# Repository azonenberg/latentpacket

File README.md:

# latentpacket
The LATENTPACKET network infrastructure platform

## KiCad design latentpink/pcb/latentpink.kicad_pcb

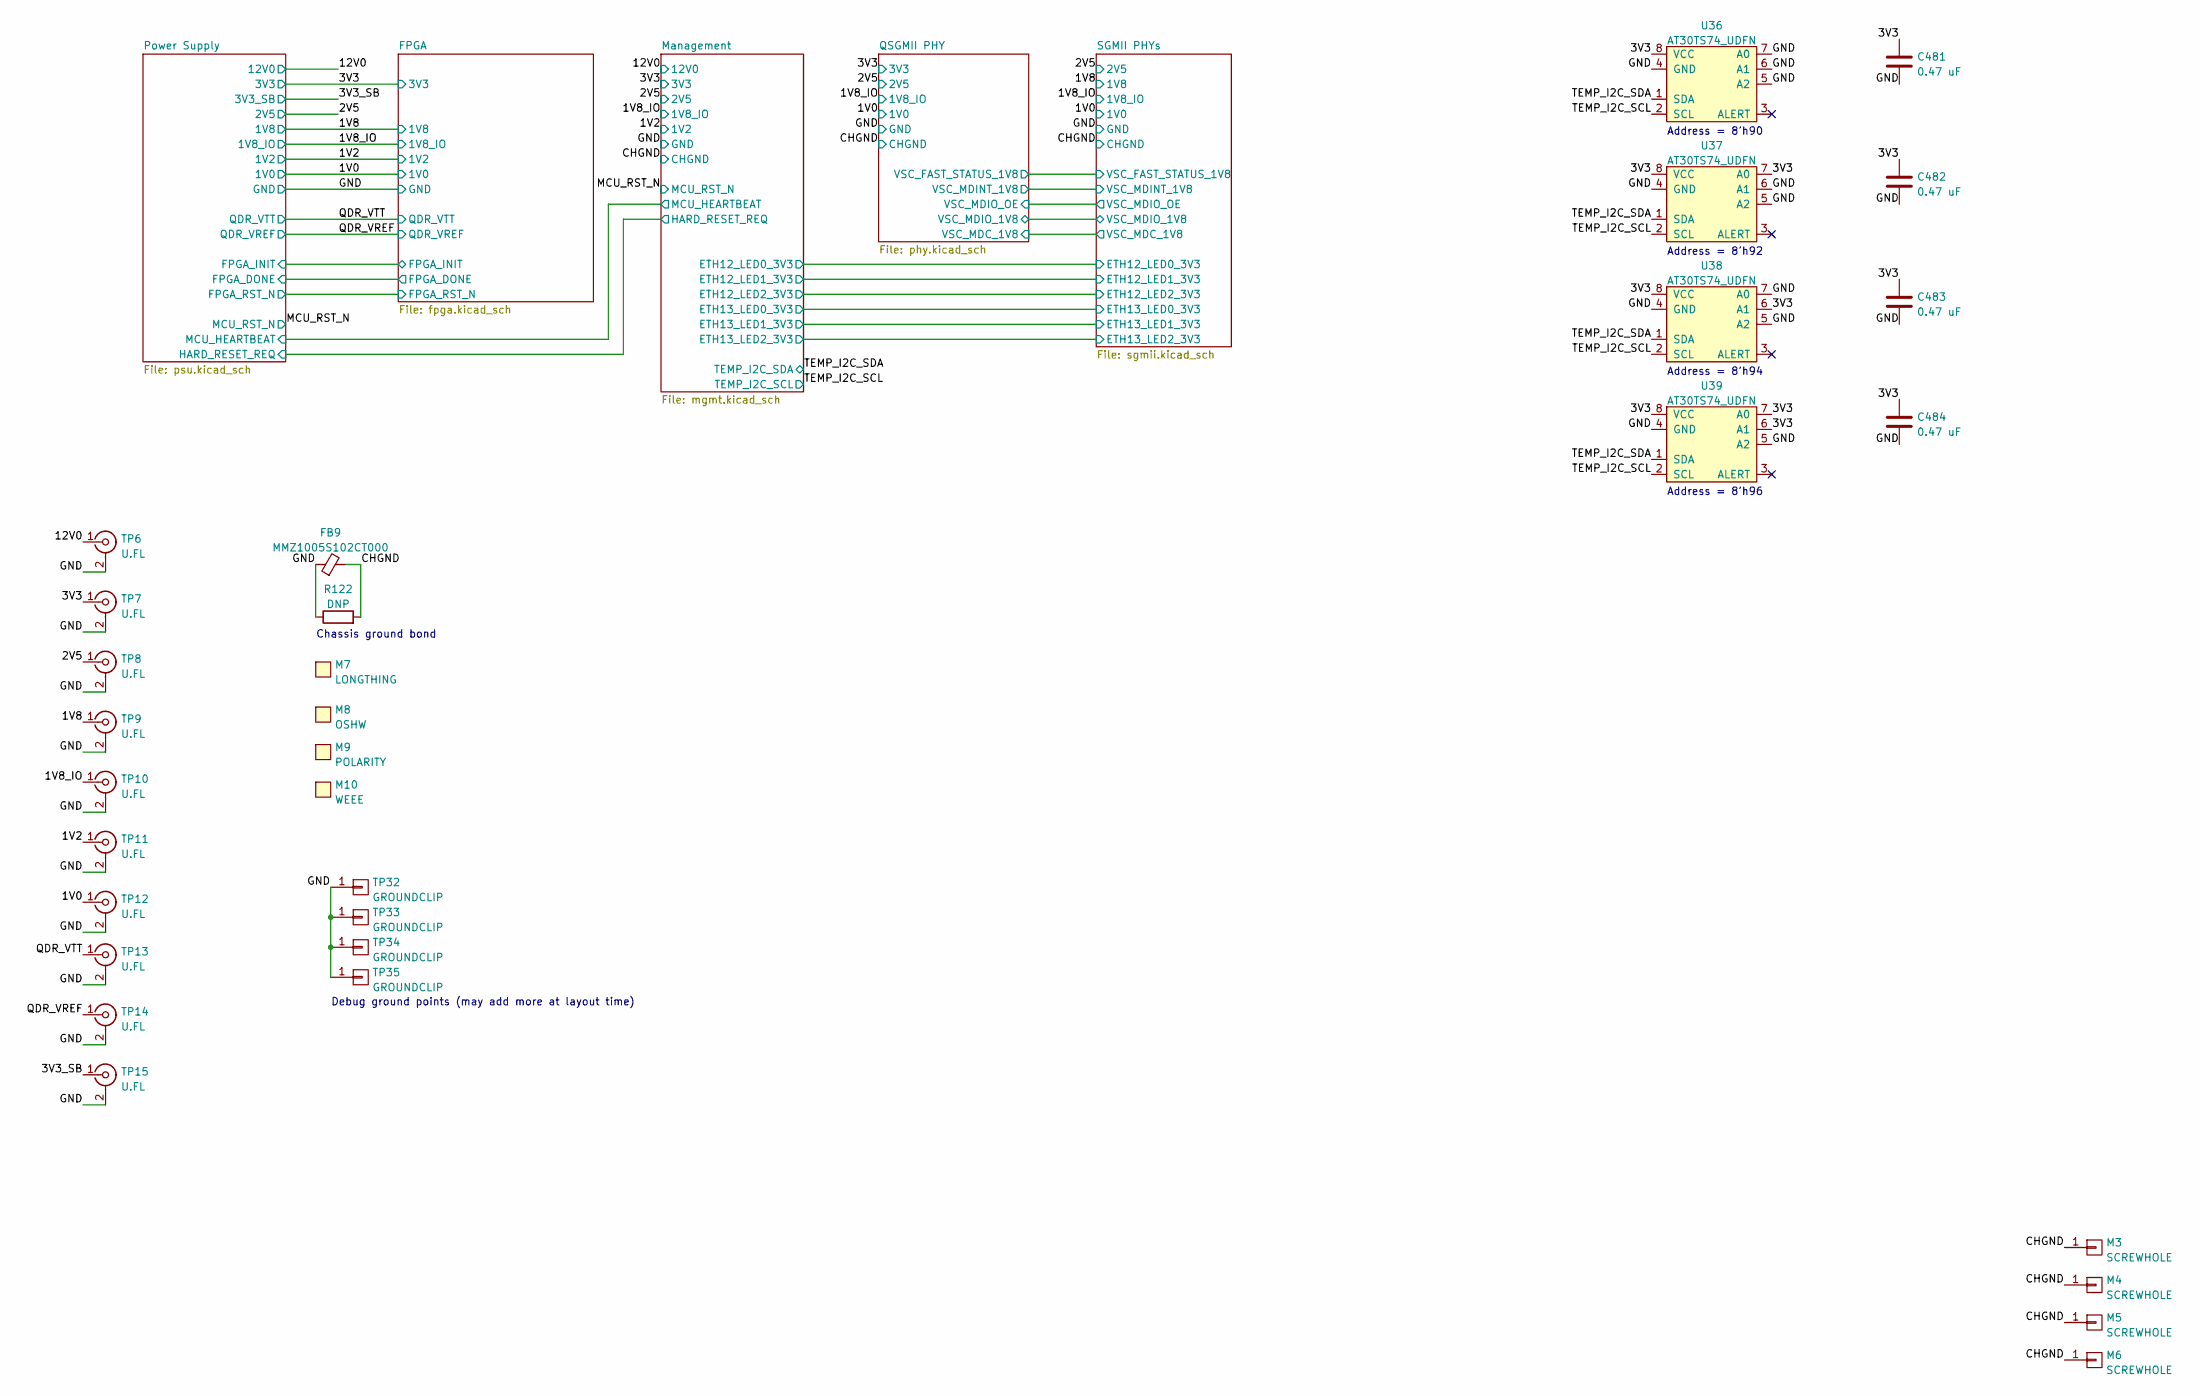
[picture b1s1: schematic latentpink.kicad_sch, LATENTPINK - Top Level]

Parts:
C481, C482, C483, C484: 0.47 uF; EIA_0402_CAP_NOSILK
FB9: MMZ1005S102CT000; EIA_0402_CAP_NOSILK
M3, M4, M5, M6: SCREWHOLE; MECHANICAL_CLEARANCEHOLE_4_40
M7: LONGTHING; LONGTHING-1200DPI
M8: OSHW; Logo_silk_OSHW_6x6mm
M9: POLARITY; Logo_silk_polarity_center_5x1.4mm
M10: WEEE; Logo_silk_WEEE_3.4x5mm
R122: DNP; EIA_1206_CAP_NOSILK
TP6, TP7, TP8, TP9, TP10, TP11, TP12, TP13, TP14, TP15: U.FL; CONN_U.FL_TE_1909763-1
TP32, TP33, TP34, TP35: GROUNDCLIP; TESTPOINT_SMT_KEYSTONE_5016
U36, U37, U38, U39: AT30TS74_UDFN; DFN_8_0.5MM_2x3MM_TALL

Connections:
/1V0: TP12.1 (In); also elsewhere on the board
/1V2: TP11.1 (In); also elsewhere on the board
/1V8: TP9.1 (In); also elsewhere on the board
/1V8_IO: TP10.1 (In); also elsewhere on the board
/2V5: TP8.1 (In); also elsewhere on the board
/3V3: C481.1, C482.1, C483.1, C484.1, TP7.1 (In), U36.8 (VCC), U37.7 (A0), U37.8 (VCC), U38.6 (A1), U38.8 (VCC), U39.6 (A1), U39.7 (A0), U39.8 (VCC); also elsewhere on the board
/3V3_SB: TP15.1 (In); also elsewhere on the board
/12V0: TP6.1 (In); also elsewhere on the board
/CHGND: FB9.2, M3.1, M4.1, M5.1, M6.1, R122.2; also elsewhere on the board
/GND: C481.2, C482.2, C483.2, C484.2, FB9.1, R122.1, TP6.2 (Ext), TP7.2 (Ext), TP8.2 (Ext), TP9.2 (Ext), TP10.2 (Ext), TP11.2 (Ext), TP12.2 (Ext), TP13.2 (Ext), TP14.2 (Ext), TP15.2 (Ext), TP32.1, TP33.1, TP34.1, TP35.1, U36.4 (GND), U36.5 (A2), U36.6 (A1), U36.7 (A0), U37.4 (GND), U37.5 (A2), U37.6 (A1), U38.4 (GND), U38.5 (A2), U38.7 (A0), U39.4 (GND), U39.5 (A2); also elsewhere on the board
/QDR_VREF: TP14.1 (In); also elsewhere on the board
/QDR_VTT: TP13.1 (In); also elsewhere on the board
/TEMP_I2C_SCL: U36.2 (SCL), U37.2 (SCL), U38.2 (SCL), U39.2 (SCL); also elsewhere on the board
/TEMP_I2C_SDA: U36.1 (SDA), U37.1 (SDA), U38.1 (SDA), U39.1 (SDA); also elsewhere on the board

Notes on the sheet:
Address = 8'h90
Chassis ground bond
Address = 8'h94
Address = 8'h92
Address = 8'h96
Debug ground points (may add more at layout time)

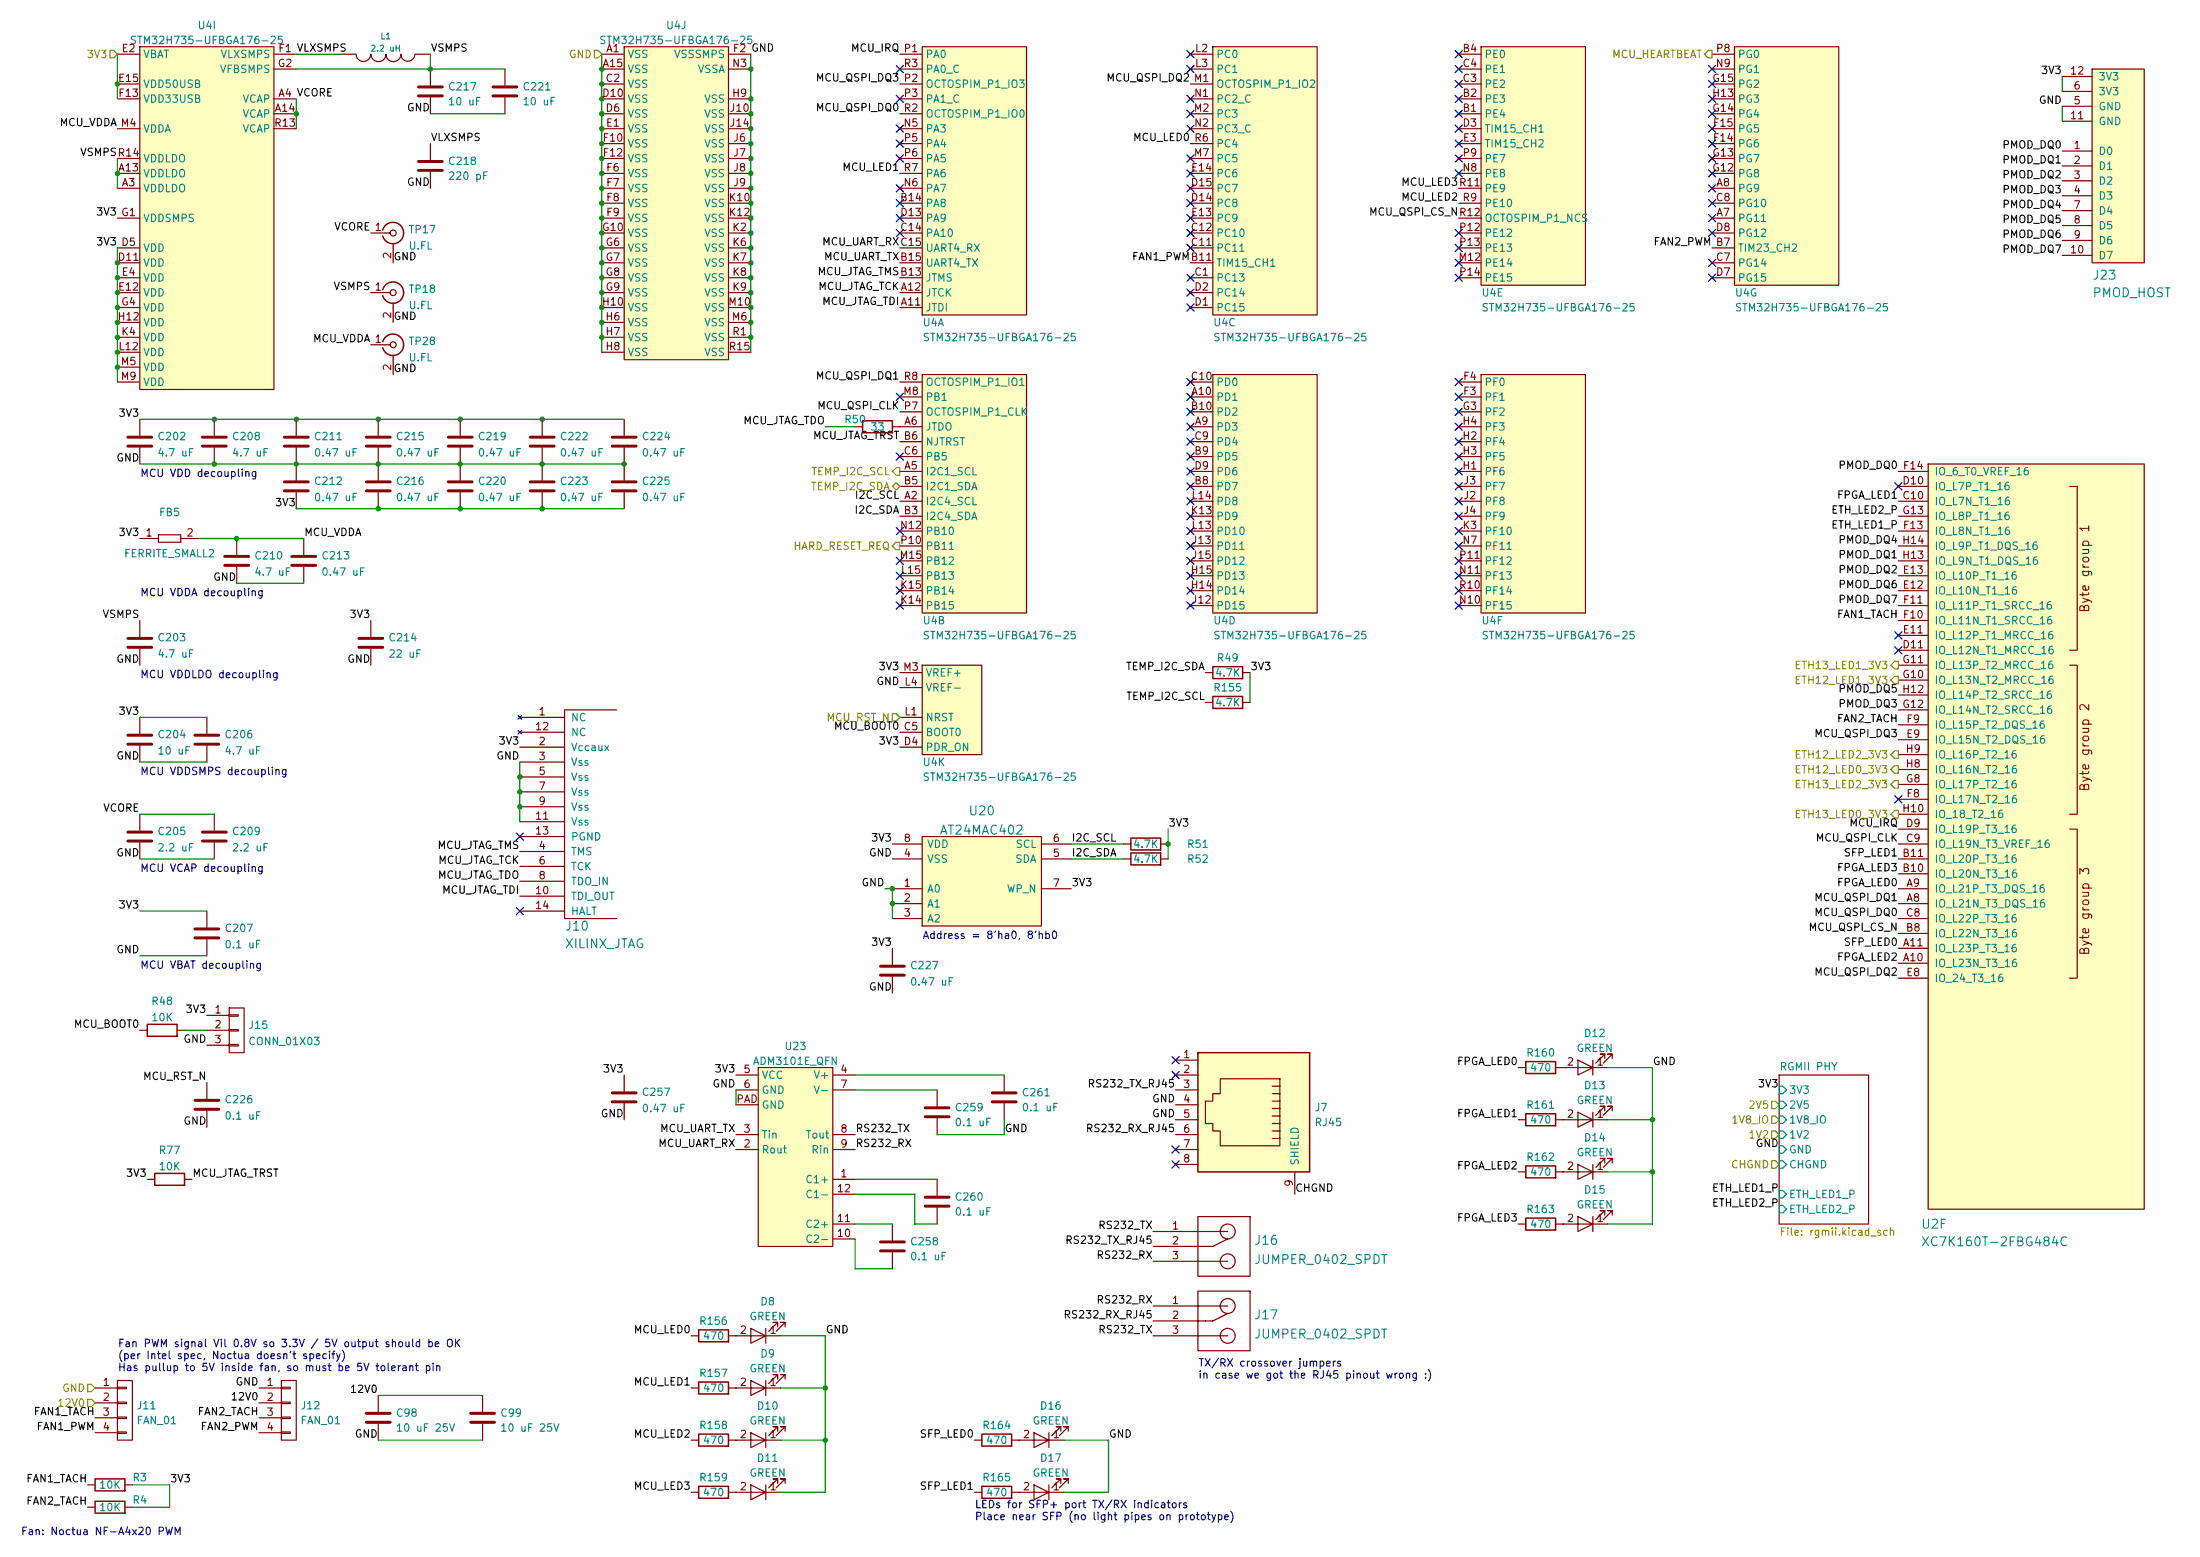
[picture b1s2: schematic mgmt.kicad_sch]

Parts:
C98, C99: 10 uF 25V; EIA_1210_CAP_NOSILK
C202, C203, C206, C208, C210: 4.7 uF; EIA_0603_CAP_NOSILK
C204, C217, C221: 10 uF; EIA_0805_CAP_NOSILK
C205, C209: 2.2 uF; EIA_0603_CAP_NOSILK
C207, C226, C258, C259, C260, C261: 0.1 uF; EIA_0402_CAP_NOSILK
C211, C212, C213, C215, C216, C219, C220, C222, C223, C224, C225, C227, C257: 0.47 uF; EIA_0402_CAP_NOSILK
C214: 22 uF; EIA_1206_CAP_NOSILK
C218: 220 pF; EIA_0402_CAP_NOSILK
D8, D9, D10, D11, D12, D13, D14, D15, D16, D17: GREEN; EIA_0603_LED
FB5: FERRITE_SMALL2; EIA_0603_INDUCTOR_NOSILK
J7: RJ45; CONN_RJ45_BELSTEWART_SS-7188S-A-PG4-1-BA-xx
J10: XILINX_JTAG; XILINX_JTAG_PTH_MOLEX_0878311420
J11, J12: FAN_01; CONN_MOLEX_KK_0470531000
J15: CONN_01X03; CONN_HEADER_2.54MM_1x3
J16, J17: JUMPER_0402_SPDT; EIA_0402_JUMPER
J23: PMOD_HOST; CONN_HEADER_2.54MM_2x6_RA_PMOD_HOST
L1: 2.2 uH; EIA_1210_CAP_NOSILK
R3, R4, R48, R77: 10K; EIA_0402_RES_NOSILK
R49, R51, R52, R155: 4.7K; EIA_0402_RES_NOSILK
R50: 33; EIA_0402_RES_NOSILK
R156, R157, R158, R159, R160, R161, R162, R163, R164, R165: 470; EIA_0402_RES_NOSILK
TP17, TP18, TP28: U.FL; CONN_U.FL_TE_1909763-1
U2: XC7K160T-2FBG484C; BGA_484_22x22_FULLARRAY_1MM
U4: STM32H735-UFBGA176-25; BGA_201_10x10_DEPOP_0.65MM_OSHPARK
U20: AT24MAC402; DFN_8_0.5MM_2x3MM_TALL
U23: ADM3101E_QFN; QFN_12_0.5MM_3x3MM

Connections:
/3V3: C202.1, C204.1, C206.1, C207.1, C208.1, C211.1, C212.2, C214.1, C215.1, C216.2, C219.1, C220.2, C222.1, C223.2, C224.1, C225.2, C227.1, C257.1, FB5.1, J10.2 (Vccaux), J15.1, J23.6 (3V3), J23.12 (3V3), R3.2, R4.2, R49.2, R51.2, R52.2, R77.1, R155.2, U4.D4 (PDR_ON), U4.D5 (VDD), U4.D11 (VDD), U4.E2 (VBAT), U4.E4 (VDD), U4.E12 (VDD), U4.E15 (VDD50USB), U4.F13 (VDD33USB), U4.G1 (VDDSMPS), U4.G4 (VDD), U4.H12 (VDD), U4.K4 (VDD), U4.L12 (VDD), U4.M3 (VREF+), U4.M5 (VDD), U4.M9 (VDD), U20.7 (WP_N), U20.8 (VDD), U23.5 (VCC); also elsewhere on the board
/12V0: C98.1, C99.1, J11.2, J12.2; also elsewhere on the board
/CHGND: J7.9 (SHIELD); also elsewhere on the board
/GND: C98.2, C99.2, C202.2, C203.2, C204.2, C205.2, C206.2, C207.2, C208.2, C209.2, C210.2, C211.2, C212.1, C213.2, C214.2, C215.2, C216.1, C217.2, C218.2, C219.2, C220.1, C221.2, C222.2, C223.1, C224.2, C225.1, C226.2, C227.2, C257.2, C259.2, C261.2, D8.1 (K), D9.1 (K), D10.1 (K), D11.1 (K), D12.1 (K), D13.1 (K), D14.1 (K), D15.1 (K), D16.1 (K), D17.1 (K), J7.4, J7.5, J10.3 (Vss), J10.5 (Vss), J10.7 (Vss), J10.9 (Vss), J10.11 (Vss), J11.1, J12.1, J15.3, J23.5 (GND), J23.11 (GND), TP17.2 (Ext), TP18.2 (Ext), TP28.2 (Ext), U4.A1 (VSS), U4.A15 (VSS), U4.C2 (VSS), U4.D6 (VSS), U4.D10 (VSS), U4.E1 (VSS), U4.F2 (VSSSMPS), U4.F6 (VSS), U4.F7 (VSS), U4.F8 (VSS), U4.F9 (VSS), U4.F10 (VSS), U4.F12 (VSS), U4.G6 (VSS), U4.G7 (VSS), U4.G8 (VSS), U4.G9 (VSS), U4.G10 (VSS), U4.H6 (VSS), U4.H7 (VSS), U4.H8 (VSS), U4.H9 (VSS), U4.H10 (VSS), U4.J6 (VSS), U4.J7 (VSS), U4.J8 (VSS), U4.J9 (VSS), U4.J10 (VSS), U4.J14 (VSS), U4.K2 (VSS), U4.K6 (VSS), U4.K7 (VSS), U4.K8 (VSS), U4.K9 (VSS), U4.K10 (VSS), U4.K12 (VSS), U4.L4 (VREF-), U4.M6 (VSS), U4.M10 (VSS), U4.N3 (VSSA), U4.R1 (VSS), U4.R15 (VSS), U20.1 (A0), U20.2 (A1), U20.3 (A2), U20.4 (VSS), U23.6 (GND), U23.PAD (GND); also elsewhere on the board
/MCU_RST_N: C226.1, U4.L1 (NRST); also elsewhere on the board
/Management/ETH12_LED0_3V3: U2.H8 (IO_L16N_T2_16); also elsewhere on the board
/Management/ETH12_LED1_3V3: U2.G10 (IO_L13N_T2_MRCC_16); also elsewhere on the board
/Management/ETH12_LED2_3V3: U2.H9 (IO_L16P_T2_16); also elsewhere on the board
/Management/ETH13_LED0_3V3: U2.H10 (IO_18_T2_16); also elsewhere on the board
/Management/ETH13_LED1_3V3: U2.G11 (IO_L13P_T2_MRCC_16); also elsewhere on the board
/Management/ETH13_LED2_3V3: U2.G8 (IO_L17P_T2_16); also elsewhere on the board
/Management/ETH_LED1_P: U2.F13 (IO_L8N_T1_16); also elsewhere on the board
/Management/ETH_LED2_P: U2.G13 (IO_L8P_T1_16); also elsewhere on the board
/Management/FAN1_PWM: J11.4, U4.B11 (TIM15_CH1)
/Management/FAN1_TACH: J11.3, R3.1, U2.F10 (IO_L11N_T1_SRCC_16)
/Management/FAN2_PWM: J12.4, U4.B7 (TIM23_CH2)
/Management/FAN2_TACH: J12.3, R4.1, U2.F9 (IO_L15P_T2_DQS_16)
/Management/FPGA_LED0: R160.1, U2.A9 (IO_L21P_T3_DQS_16)
/Management/FPGA_LED1: R161.1, U2.C10 (IO_L7N_T1_16)
/Management/FPGA_LED2: R162.1, U2.A10 (IO_L23N_T3_16)
/Management/FPGA_LED3: R163.1, U2.B10 (IO_L20N_T3_16)
/Management/HARD_RESET_REQ: U4.P10 (PB11); also elsewhere on the board
/Management/I2C_SCL: R51.1, U4.A2 (I2C4_SCL), U20.6 (SCL)
/Management/I2C_SDA: R52.1, U4.B3 (I2C4_SDA), U20.5 (SDA)
/Management/MCU_BOOT0: R48.1, U4.C5 (BOOT0)
/Management/MCU_HEARTBEAT: U4.P8 (PG0); also elsewhere on the board
/Management/MCU_IRQ: U2.D9 (IO_L19P_T3_16), U4.P1 (PA0)
/Management/MCU_JTAG_TCK: J10.6 (TCK), U4.A12 (JTCK)
/Management/MCU_JTAG_TDI: J10.10 (TDI_OUT), U4.A11 (JTDI)
/Management/MCU_JTAG_TDO: J10.8 (TDO_IN), R50.1
/Management/MCU_JTAG_TMS: J10.4 (TMS), U4.B13 (JTMS)
/Management/MCU_JTAG_TRST: R77.2, U4.B6 (NJTRST)
/Management/MCU_LED0: R156.1, U4.R6 (PC4)
/Management/MCU_LED1: R157.1, U4.R7 (PA6)
/Management/MCU_LED2: R158.1, U4.R9 (PE10)
/Management/MCU_LED3: R159.1, U4.R11 (PE9)
/Management/MCU_QSPI_CLK: U2.C9 (IO_L19N_T3_VREF_16), U4.P7 (OCTOSPIM_P1_CLK)
/Management/MCU_QSPI_CS_N: U2.B8 (IO_L22N_T3_16), U4.R12 (OCTOSPIM_P1_NCS)
/Management/MCU_QSPI_DQ0: U2.C8 (IO_L22P_T3_16), U4.R2 (OCTOSPIM_P1_IO0)
/Management/MCU_QSPI_DQ1: U2.A8 (IO_L21N_T3_DQS_16), U4.R8 (OCTOSPIM_P1_IO1)
/Management/MCU_QSPI_DQ2: U2.E8 (IO_24_T3_16), U4.M1 (OCTOSPIM_P1_IO2)
/Management/MCU_QSPI_DQ3: U2.E9 (IO_L15N_T2_DQS_16), U4.P2 (OCTOSPIM_P1_IO3)
/Management/MCU_UART_RX: U4.C15 (UART4_RX), U23.2 (Rout)
/Management/MCU_UART_TX: U4.B15 (UART4_TX), U23.3 (Tin)
/Management/MCU_VDDA: C210.1, C213.1, FB5.2, TP28.1 (In), U4.M4 (VDDA)
/Management/PMOD_DQ0: J23.1 (D0), U2.F14 (IO_6_T0_VREF_16)
/Management/PMOD_DQ1: J23.2 (D1), U2.H13 (IO_L9N_T1_DQS_16)
/Management/PMOD_DQ2: J23.3 (D2), U2.E13 (IO_L10P_T1_16)
/Management/PMOD_DQ3: J23.4 (D3), U2.G12 (IO_L14N_T2_SRCC_16)
/Management/PMOD_DQ4: J23.7 (D4), U2.H14 (IO_L9P_T1_DQS_16)
/Management/PMOD_DQ5: J23.8 (D5), U2.H12 (IO_L14P_T2_SRCC_16)
/Management/PMOD_DQ6: J23.9 (D6), U2.E12 (IO_L10N_T1_16)
/Management/PMOD_DQ7: J23.10 (D7), U2.F11 (IO_L11P_T1_SRCC_16)
/Management/RS232_RX: J16.3, J17.1, U23.9 (Rin)
/Management/RS232_RX_RJ45: J7.6, J17.2
/Management/RS232_TX: J16.1, J17.3, U23.8 (Tout)
/Management/RS232_TX_RJ45: J7.3, J16.2
/Management/SFP_LED0: R164.1, U2.A11 (IO_L23P_T3_16)
/Management/SFP_LED1: R165.1, U2.B11 (IO_L20P_T3_16)
/Management/VCORE: C205.1, C209.1, TP17.1 (In), U4.A4 (VCAP), U4.A14 (VCAP), U4.R13 (VCAP)
/Management/VLXSMPS: C218.1, L1.2, U4.F1 (VLXSMPS)
/Management/VSMPS: C203.1, C217.1, C221.1, L1.1, TP18.1 (In), U4.A3 (VDDLDO), U4.A13 (VDDLDO), U4.G2 (VFBSMPS), U4.R14 (VDDLDO)
/TEMP_I2C_SCL: R155.1, U4.A5 (I2C1_SCL); also elsewhere on the board
/TEMP_I2C_SDA: R49.1, U4.B5 (I2C1_SDA); also elsewhere on the board
unnamed: C258.1, U23.11 (C2+)
unnamed: C258.2, U23.10 (C2-)
unnamed: C259.1, U23.7 (V-)
unnamed: C260.1, U23.1 (C1+)
unnamed: C260.2, U23.12 (C1-)
unnamed: C261.1, U23.4 (V+)
unnamed: D8.2 (A), R156.2
unnamed: D9.2 (A), R157.2
unnamed: D10.2 (A), R158.2
unnamed: D11.2 (A), R159.2
unnamed: D12.2 (A), R160.2
unnamed: D13.2 (A), R161.2
unnamed: D14.2 (A), R162.2
unnamed: D15.2 (A), R163.2
unnamed: D16.2 (A), R164.2
unnamed: D17.2 (A), R165.2
unnamed: J15.2, R48.2
unnamed: R50.2, U4.A6 (JTDO)

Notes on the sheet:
Address = 8'ha0, 8'hb0
MCU VDD decoupling
MCU VDDA decoupling
Fan: Noctua NF-A4x20 PWM
MCU VDDLDO decoupling
TX/RX crossover jumpers in case we got the RJ45 pinout wrong :)
Fan PWM signal Vil 0.8V so 3.3V / 5V output should be OK (per Intel spec, Noctua doesn't specify) Has pullup to 5V inside fan, so must be 5V tolerant pin
LEDs for SFP+ port TX/RX indicators Place near SFP (no light pipes on prototype)
MCU VCAP decoupling
MCU VBAT decoupling
MCU VDDSMPS decoupling

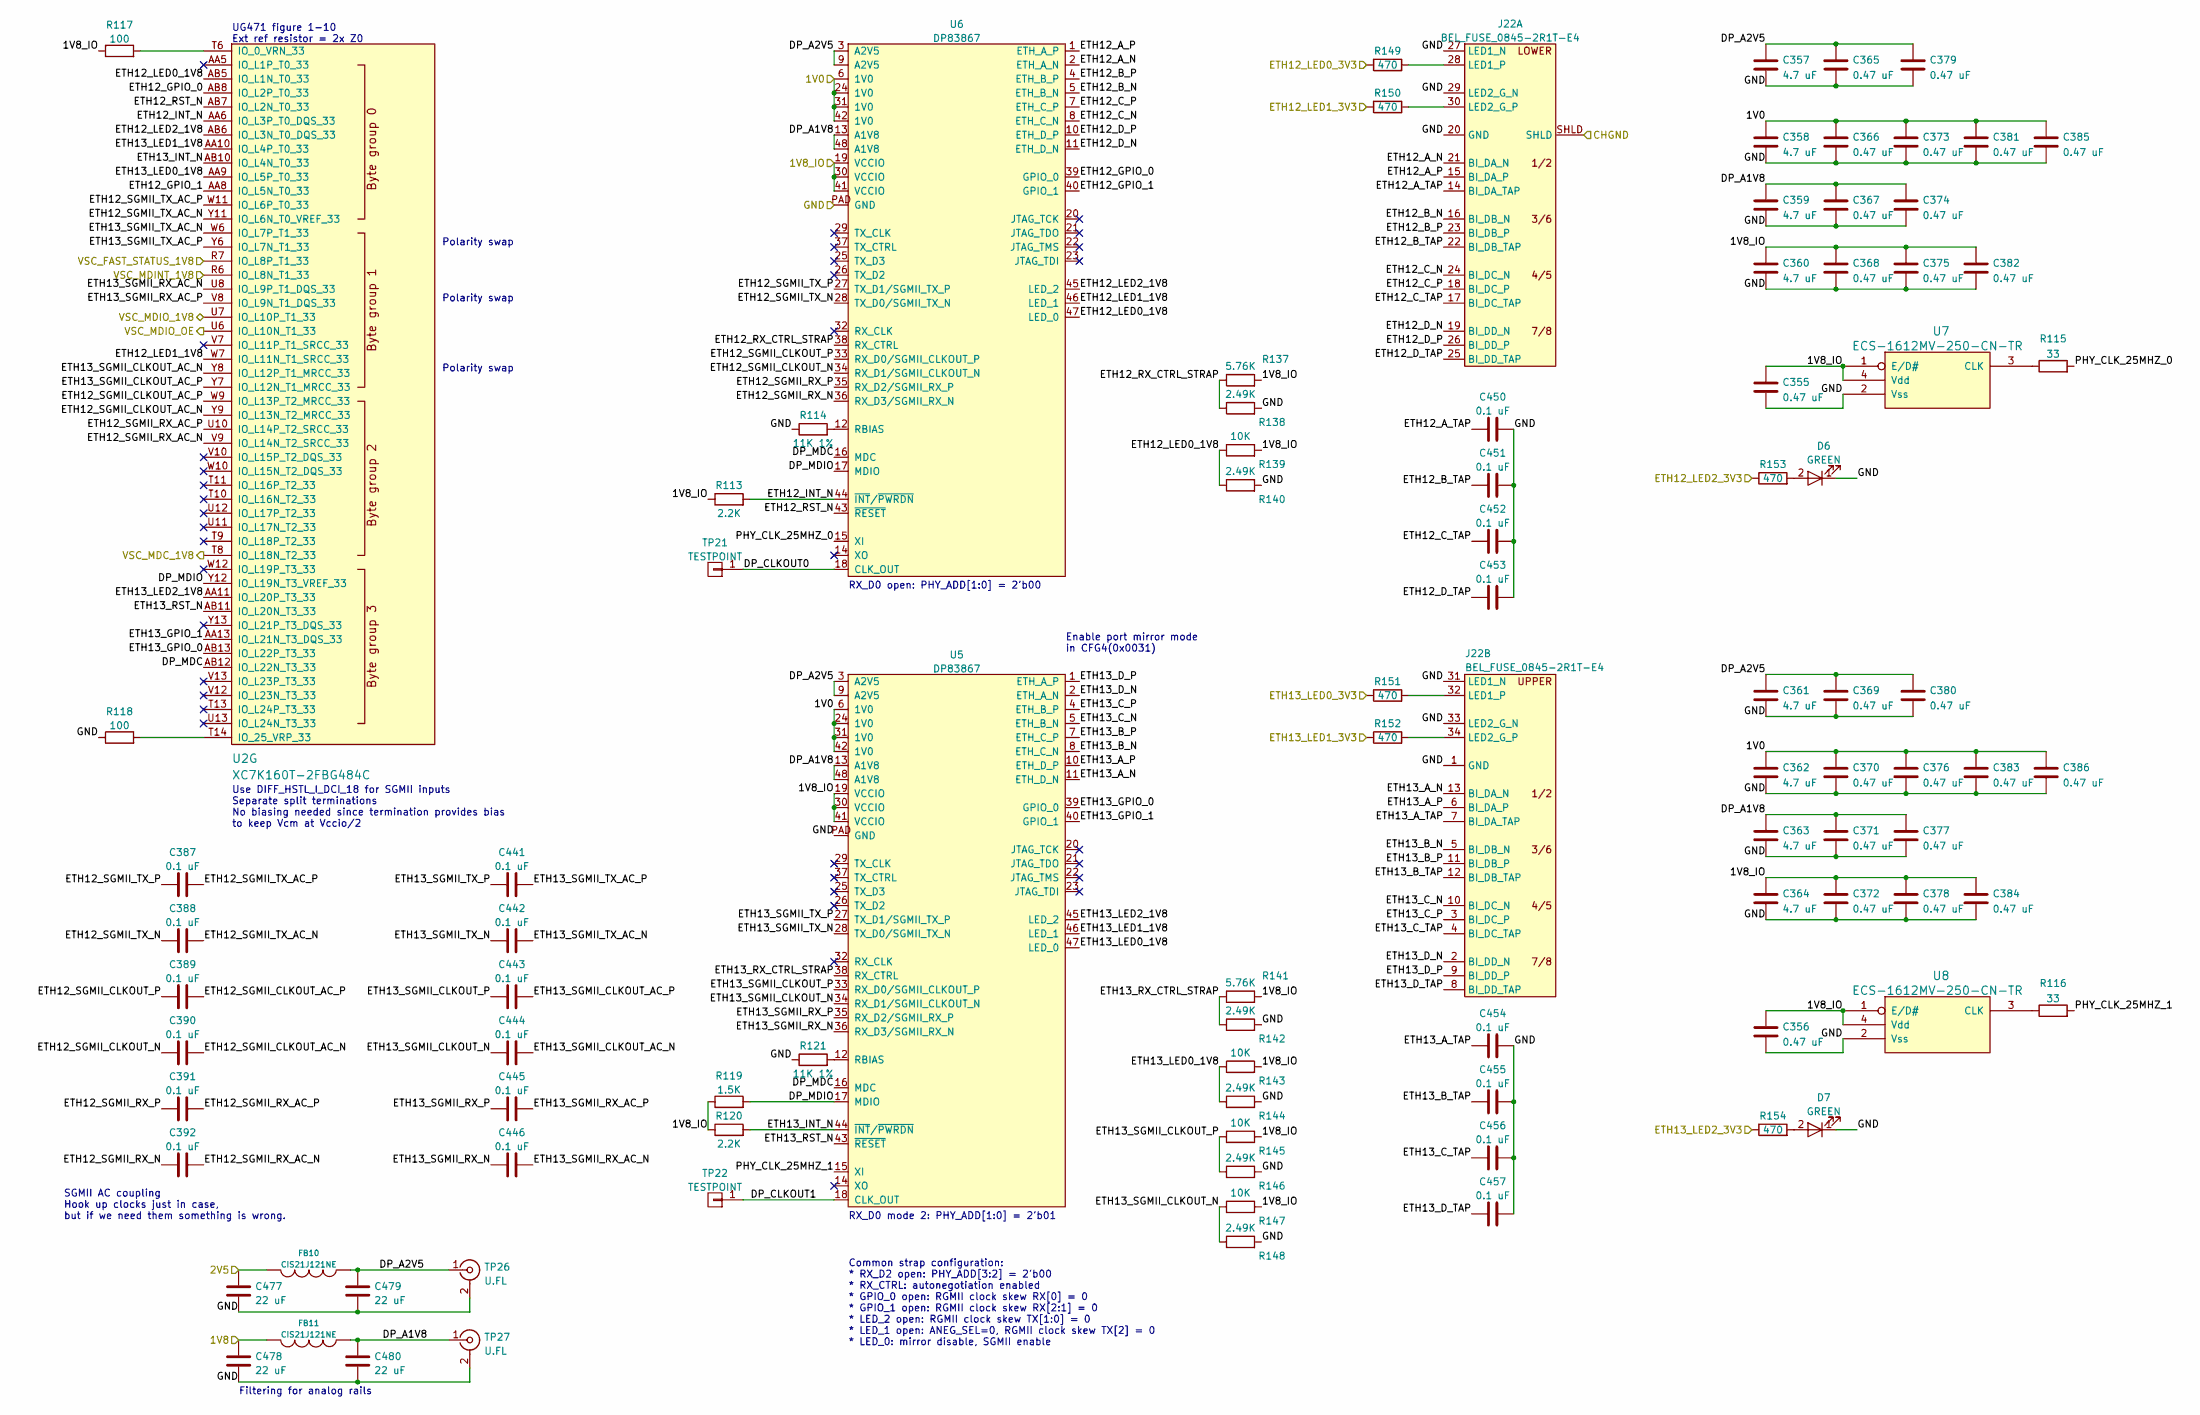
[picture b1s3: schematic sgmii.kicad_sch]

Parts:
C355, C356, C365, C366, C367, C368, C369, C370, C371, C372, C373, C374, C375, C376, C377, C378, C379, C380, C381, C382, C383, C384, C385, C386: 0.47 uF; EIA_0402_CAP_NOSILK
C357, C358, C359, C360, C361, C362, C363, C364: 4.7 uF; EIA_0603_CAP_NOSILK
C387, C388, C389, C390, C391, C392, C441, C442, C443, C444, C445, C446, C450, C451, C452, C453, C454, C455, C456, C457: 0.1 uF; EIA_0402_CAP_NOSILK
C477, C478, C479, C480: 22 uF; EIA_1206_CAP_NOSILK
D6, D7: GREEN; EIA_0603_LED
FB10, FB11: CIS21J121NE; EIA_0805_INDUCTOR_NOSILK
J22: BEL_FUSE_0845-2R1T-E4; CONN_RJ45_BELFUSE_0845-2R1T-E4
R113, R120: 2.2K; EIA_0402_RES_NOSILK
R114, R121: 11K 1%; EIA_0402_RES_NOSILK
R115, R116: 33; EIA_0402_RES_NOSILK
R117, R118: 100; EIA_0402_RES_NOSILK
R119: 1.5K; EIA_0402_RES_NOSILK
R137, R141: 5.76K; EIA_0402_RES_NOSILK
R138, R140, R142, R144, R146, R148: 2.49K; EIA_0402_RES_NOSILK
R139, R143, R145, R147: 10K; EIA_0402_RES_NOSILK
R149, R150, R151, R152, R153, R154: 470; EIA_0402_RES_NOSILK
TP21, TP22: TESTPOINT; TESTPOINT_SMT_0.5MM
TP26, TP27: U.FL; CONN_U.FL_TE_1909763-1
U2: XC7K160T-2FBG484C; BGA_484_22x22_FULLARRAY_1MM
U5, U6: DP83867; QFN_48_0.5MM_7x7MM
U7, U8: ECS-1612MV-250-CN-TR; OSCILLATOR_1.6x1.2

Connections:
/1V0: C358.1, C362.1, C366.1, C370.1, C373.1, C376.1, C381.1, C383.1, C385.1, C386.1, U5.6 (1V0), U5.24 (1V0), U5.31 (1V0), U5.42 (1V0), U6.6 (1V0), U6.24 (1V0), U6.31 (1V0), U6.42 (1V0); also elsewhere on the board
/1V8: C478.1, FB11.2; also elsewhere on the board
/1V8_IO: C355.1, C356.1, C360.1, C364.1, C368.1, C372.1, C375.1, C378.1, C382.1, C384.1, R113.1, R117.1, R119.1, R120.1, R137.2, R139.2, R141.2, R143.2, R145.2, R147.2, U5.19 (VCCIO), U5.30 (VCCIO), U5.41 (VCCIO), U6.19 (VCCIO), U6.30 (VCCIO), U6.41 (VCCIO), U7.1 (E/D#), U7.4 (Vdd), U8.1 (E/D#), U8.4 (Vdd); also elsewhere on the board
/2V5: C477.1, FB10.2; also elsewhere on the board
/CHGND: J22.SHLD; also elsewhere on the board
/GND: C355.2, C356.2, C357.2, C358.2, C359.2, C360.2, C361.2, C362.2, C363.2, C364.2, C365.2, C366.2, C367.2, C368.2, C369.2, C370.2, C371.2, C372.2, C373.2, C374.2, C375.2, C376.2, C377.2, C378.2, C379.2, C380.2, C381.2, C382.2, C383.2, C384.2, C385.2, C386.2, C450.2, C451.2, C452.2, C453.2, C454.2, C455.2, C456.2, C457.2, C477.2, C478.2, C479.2, C480.2, D6.1 (K), D7.1 (K), J22.1 (GND), J22.20 (GND), J22.27 (LED1_N), J22.29 (LED2_G_N), J22.31 (LED1_N), J22.33 (LED2_G_N), R114.1, R118.1, R121.1, R138.2, R140.2, R142.2, R144.2, R146.2, R148.2, TP26.2 (Ext), TP27.2 (Ext), U5.PAD (GND), U6.PAD (GND), U7.2 (Vss), U8.2 (Vss); also elsewhere on the board
/Management/ETH12_LED0_3V3: R149.1; also elsewhere on the board
/Management/ETH12_LED1_3V3: R150.1; also elsewhere on the board
/Management/ETH12_LED2_3V3: R153.1; also elsewhere on the board
/Management/ETH13_LED0_3V3: R151.1; also elsewhere on the board
/Management/ETH13_LED1_3V3: R152.1; also elsewhere on the board
/Management/ETH13_LED2_3V3: R154.1; also elsewhere on the board
/QSGMII PHY/VSC_FAST_STATUS_1V8: U2.R7 (IO_L8P_T1_33); also elsewhere on the board
/QSGMII PHY/VSC_MDC_1V8: U2.T8 (IO_L18N_T2_33); also elsewhere on the board
/QSGMII PHY/VSC_MDINT_1V8: U2.R6 (IO_L8N_T1_33); also elsewhere on the board
/QSGMII PHY/VSC_MDIO_1V8: U2.U7 (IO_L10P_T1_33); also elsewhere on the board
/QSGMII PHY/VSC_MDIO_OE: U2.U6 (IO_L10N_T1_33); also elsewhere on the board
/SGMII PHYs/DP_A1V8: C359.1, C363.1, C367.1, C371.1, C374.1, C377.1, C480.1, FB11.1, TP27.1 (In), U5.13 (A1V8), U5.48 (A1V8), U6.13 (A1V8), U6.48 (A1V8)
/SGMII PHYs/DP_A2V5: C357.1, C361.1, C365.1, C369.1, C379.1, C380.1, C479.1, FB10.1, TP26.1 (In), U5.3 (A2V5), U5.9 (A2V5), U6.3 (A2V5), U6.9 (A2V5)
/SGMII PHYs/DP_CLKOUT0: TP21.1, U6.18 (CLK_OUT)
/SGMII PHYs/DP_CLKOUT1: TP22.1, U5.18 (CLK_OUT)
/SGMII PHYs/DP_MDC: U2.AB12 (IO_L22N_T3_33), U5.16 (MDC), U6.16 (MDC)
/SGMII PHYs/DP_MDIO: R119.2, U2.Y12 (IO_L19N_T3_VREF_33), U5.17 (MDIO), U6.17 (MDIO)
/SGMII PHYs/ETH12_A_N: J22.21 (BI_DA_N), U6.2 (ETH_A_N)
/SGMII PHYs/ETH12_A_P: J22.15 (BI_DA_P), U6.1 (ETH_A_P)
/SGMII PHYs/ETH12_A_TAP: C450.1, J22.14 (BI_DA_TAP)
/SGMII PHYs/ETH12_B_N: J22.16 (BI_DB_N), U6.5 (ETH_B_N)
/SGMII PHYs/ETH12_B_P: J22.23 (BI_DB_P), U6.4 (ETH_B_P)
/SGMII PHYs/ETH12_B_TAP: C451.1, J22.22 (BI_DB_TAP)
/SGMII PHYs/ETH12_C_N: J22.24 (BI_DC_N), U6.8 (ETH_C_N)
/SGMII PHYs/ETH12_C_P: J22.18 (BI_DC_P), U6.7 (ETH_C_P)
/SGMII PHYs/ETH12_C_TAP: C452.1, J22.17 (BI_DC_TAP)
/SGMII PHYs/ETH12_D_N: J22.19 (BI_DD_N), U6.11 (ETH_D_N)
/SGMII PHYs/ETH12_D_P: J22.26 (BI_DD_P), U6.10 (ETH_D_P)
/SGMII PHYs/ETH12_D_TAP: C453.1, J22.25 (BI_DD_TAP)
/SGMII PHYs/ETH12_GPIO_0: U2.AB8 (IO_L2P_T0_33), U6.39 (GPIO_0)
/SGMII PHYs/ETH12_GPIO_1: U2.AA8 (IO_L5N_T0_33), U6.40 (GPIO_1)
/SGMII PHYs/ETH12_INT_N: R113.2, U2.AA6 (IO_L3P_T0_DQS_33), U6.44 (~INT/~PWRDN)
/SGMII PHYs/ETH12_LED0_1V8: R139.1, R140.1, U2.AB5 (IO_L1N_T0_33), U6.47 (LED_0)
/SGMII PHYs/ETH12_LED1_1V8: U2.W7 (IO_L11N_T1_SRCC_33), U6.46 (LED_1)
/SGMII PHYs/ETH12_LED2_1V8: U2.AB6 (IO_L3N_T0_DQS_33), U6.45 (LED_2)
/SGMII PHYs/ETH12_RST_N: U2.AB7 (IO_L2N_T0_33), U6.43 (~RESET)
/SGMII PHYs/ETH12_RX_CTRL_STRAP: R137.1, R138.1, U6.38 (RX_CTRL)
/SGMII PHYs/ETH12_SGMII_CLKOUT_AC_N: C390.2, U2.Y9 (IO_L13N_T2_MRCC_33)
/SGMII PHYs/ETH12_SGMII_CLKOUT_AC_P: C389.2, U2.W9 (IO_L13P_T2_MRCC_33)
/SGMII PHYs/ETH12_SGMII_CLKOUT_N: C390.1, U6.34 (RX_D1/SGMII_CLKOUT_N)
/SGMII PHYs/ETH12_SGMII_CLKOUT_P: C389.1, U6.33 (RX_D0/SGMII_CLKOUT_P)
/SGMII PHYs/ETH12_SGMII_RX_AC_N: C392.2, U2.V9 (IO_L14N_T2_SRCC_33)
/SGMII PHYs/ETH12_SGMII_RX_AC_P: C391.2, U2.U10 (IO_L14P_T2_SRCC_33)
/SGMII PHYs/ETH12_SGMII_RX_N: C392.1, U6.36 (RX_D3/SGMII_RX_N)
/SGMII PHYs/ETH12_SGMII_RX_P: C391.1, U6.35 (RX_D2/SGMII_RX_P)
/SGMII PHYs/ETH12_SGMII_TX_AC_N: C388.2, U2.Y11 (IO_L6N_T0_VREF_33)
/SGMII PHYs/ETH12_SGMII_TX_AC_P: C387.2, U2.W11 (IO_L6P_T0_33)
/SGMII PHYs/ETH12_SGMII_TX_N: C388.1, U6.28 (TX_D0/SGMII_TX_N)
/SGMII PHYs/ETH12_SGMII_TX_P: C387.1, U6.27 (TX_D1/SGMII_TX_P)
/SGMII PHYs/ETH13_A_N: J22.13 (BI_DA_N), U5.11 (ETH_D_N)
/SGMII PHYs/ETH13_A_P: J22.6 (BI_DA_P), U5.10 (ETH_D_P)
/SGMII PHYs/ETH13_A_TAP: C454.1, J22.7 (BI_DA_TAP)
/SGMII PHYs/ETH13_B_N: J22.5 (BI_DB_N), U5.8 (ETH_C_N)
/SGMII PHYs/ETH13_B_P: J22.11 (BI_DB_P), U5.7 (ETH_C_P)
/SGMII PHYs/ETH13_B_TAP: C455.1, J22.12 (BI_DB_TAP)
/SGMII PHYs/ETH13_C_N: J22.10 (BI_DC_N), U5.5 (ETH_B_N)
/SGMII PHYs/ETH13_C_P: J22.3 (BI_DC_P), U5.4 (ETH_B_P)
/SGMII PHYs/ETH13_C_TAP: C456.1, J22.4 (BI_DC_TAP)
/SGMII PHYs/ETH13_D_N: J22.2 (BI_DD_N), U5.2 (ETH_A_N)
/SGMII PHYs/ETH13_D_P: J22.9 (BI_DD_P), U5.1 (ETH_A_P)
/SGMII PHYs/ETH13_D_TAP: C457.1, J22.8 (BI_DD_TAP)
/SGMII PHYs/ETH13_GPIO_0: U2.AB13 (IO_L22P_T3_33), U5.39 (GPIO_0)
/SGMII PHYs/ETH13_GPIO_1: U2.AA13 (IO_L21N_T3_DQS_33), U5.40 (GPIO_1)
/SGMII PHYs/ETH13_INT_N: R120.2, U2.AB10 (IO_L4N_T0_33), U5.44 (~INT/~PWRDN)
/SGMII PHYs/ETH13_LED0_1V8: R143.1, R144.1, U2.AA9 (IO_L5P_T0_33), U5.47 (LED_0)
/SGMII PHYs/ETH13_LED1_1V8: U2.AA10 (IO_L4P_T0_33), U5.46 (LED_1)
/SGMII PHYs/ETH13_LED2_1V8: U2.AA11 (IO_L20P_T3_33), U5.45 (LED_2)
/SGMII PHYs/ETH13_RST_N: U2.AB11 (IO_L20N_T3_33), U5.43 (~RESET)
/SGMII PHYs/ETH13_RX_CTRL_STRAP: R141.1, R142.1, U5.38 (RX_CTRL)
/SGMII PHYs/ETH13_SGMII_CLKOUT_AC_N: C444.2, U2.Y8 (IO_L12P_T1_MRCC_33)
/SGMII PHYs/ETH13_SGMII_CLKOUT_AC_P: C443.2, U2.Y7 (IO_L12N_T1_MRCC_33)
/SGMII PHYs/ETH13_SGMII_CLKOUT_N: C444.1, R147.1, R148.1, U5.34 (RX_D1/SGMII_CLKOUT_N)
/SGMII PHYs/ETH13_SGMII_CLKOUT_P: C443.1, R145.1, R146.1, U5.33 (RX_D0/SGMII_CLKOUT_P)
/SGMII PHYs/ETH13_SGMII_RX_AC_N: C446.2, U2.U8 (IO_L9P_T1_DQS_33)
/SGMII PHYs/ETH13_SGMII_RX_AC_P: C445.2, U2.V8 (IO_L9N_T1_DQS_33)
/SGMII PHYs/ETH13_SGMII_RX_N: C446.1, U5.36 (RX_D3/SGMII_RX_N)
/SGMII PHYs/ETH13_SGMII_RX_P: C445.1, U5.35 (RX_D2/SGMII_RX_P)
/SGMII PHYs/ETH13_SGMII_TX_AC_N: C442.2, U2.W6 (IO_L7P_T1_33)
/SGMII PHYs/ETH13_SGMII_TX_AC_P: C441.2, U2.Y6 (IO_L7N_T1_33)
/SGMII PHYs/ETH13_SGMII_TX_N: C442.1, U5.28 (TX_D0/SGMII_TX_N)
/SGMII PHYs/ETH13_SGMII_TX_P: C441.1, U5.27 (TX_D1/SGMII_TX_P)
/SGMII PHYs/PHY_CLK_25MHZ_0: R115.2, U6.15 (XI)
/SGMII PHYs/PHY_CLK_25MHZ_1: R116.2, U5.15 (XI)
unnamed: D6.2 (A), R153.2
unnamed: D7.2 (A), R154.2
unnamed: J22.28 (LED1_P), R149.2
unnamed: J22.30 (LED2_G_P), R150.2
unnamed: J22.32 (LED1_P), R151.2
unnamed: J22.34 (LED2_G_P), R152.2
unnamed: R115.1, U7.3 (CLK)
unnamed: R116.1, U8.3 (CLK)
unnamed: R117.2, U2.T6 (IO_0_VRN_33)
unnamed: R118.2, U2.T14 (IO_25_VRP_33)
unnamed: R121.2, U5.12 (RBIAS)
unnamed: R114.2, U6.12 (RBIAS)

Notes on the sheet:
Polarity swap
RX_D0 open: PHY_ADD[1:0] = 2'b00
Common strap configuration: * RX_D2 open: PHY_ADD[3:2] = 2'b00 * RX_CTRL: autonegotiation enabled * GPIO_0 open: RGMII clock skew RX[0] = 0 * GPIO_1 open: RGMII clock skew RX[2:1] = 0 * LED_2 open: RGMII clock skew TX[1:0] = 0 * LED_1 open: ANEG_SEL=0, RGMII clock skew TX[2] = 0 * LED_0: mirror dis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
Filtering for analog rails
SGMII AC coupling Hook up clocks just in case, but if we need them something is wrong.
Use DIFF_HSTL_I_DCI_18 for SGMII inputs Separate split terminations No biasing needed since termination provides bias to keep Vcm at Vccio/2
UG471 figure 1-10 Ext ref resistor = 2x Z0
Enable port mirror mode in CFG4(0x0031)
RX_D0 mode 2: PHY_ADD[1:0] = 2'b01

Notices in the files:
latentpink/firmware/super/main.cpp:
Copyright (c) 2023 Andrew D. Zonenberg and contributors
All rights reserved.
